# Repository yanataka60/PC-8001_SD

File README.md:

# PC-8001にSD-CARDからCMT形式ファイルのロード、セーブ機能

　PC-8001でSD-CARDからCMT形式ファイルのロード、セーブ機能を実現するものです。

　CMTからの読み込み実行に数分掛かっていたゲームも数十秒で実行できます。

　接続は、PC-8001本体後ろの拡張端子に接続しますが、50pフラットケーブルでの接続、50pカードエッジコネクタでの接続のどちらかを選択できます。

　なお、Arduino、ROMへ書き込むための機器が別途必要となります。

## 回路図
　KiCadフォルダ内のPC-8001_SD.pdfを参照してください。

　J5 2x25Pinコネクタを追加しています。

[回路図](https://github.com/yanataka60/PC-8001_SD/blob/main/Kicad/PC-8001_SD.pdf)

## 部品
|番号|品名|数量|備考|
| ------------ | ------------ | ------------ | ------------ |
||J1、J3のいずれか|||
|J1|2x25ボックスヘッダ|1|共立エレショップ JS-1200R-50など、秋月電子通商 PH-2x40RGなどのピンヘッダでも代用可(注1)(注5)|
|J3|50Pカードエッジコネクタ|1|せんごくネット通販 HRS CR22A-50D-2.54DSなど(注1)|
||J2、J4のいずれか|||
|J2|Micro_SD_Card_Kit|1|秋月電子通商 AE-microSD-LLCNV (注2) (注4)|
|J4|MicroSD Card Adapter|1|Arduino等に使われる5V電源に対応したもの (注4)|
|U1|74LS04|1||
|U2 U3|74LS30|2||
|U4|8255|1||
|U5|2764/28C64相当品|1||
|U6|Arduino_Pro_Mini_5V|1|Atmega328版を使用 168版は不可。(注3)|
|C1-C5|積層セラミックコンデンサ 0.1uF|5||
|C6|電解コンデンサ 16v100uF|1||
|S1|3Pスライドスイッチ|1|秋月電子通商 SS12D01G4など|
|S2|２回路２接点 スライドスイッチ|1|秋月電子通商 IS-2235-Gなど|
||ピンヘッダ|2Pin分|Arduino_Pro_MiniにはA4、A5用のピンヘッダが付いていないため別途調達が必要です 秋月電子通商 PH-1x40SGなど|
||ピンソケット(任意)|26Pin分|Arduino_Pro_Miniを取り外し可能としたい場合に調達します 秋月電子通商 FHU-1x42SGなど|
|J5|2x25Pinコネクタ|1|秋月電子通商 PH-2x40SGなど(注1)|

　　　注1)J1又はJ3のどちらかを選択して取り付けてください。

　　　注2)秋月電子通商　AE-microSD-LLCNVのJ1ジャンパはショートしてください。

　　　注3)Arduino Pro MiniはA4、A5ピンも使っています。

　　　注4)J2又はJ4のどちらかを選択して取り付けてください。

　　　注5)ピンヘッダで代用するときは、基板から若干浮かせてピンヘッダをハンダ付けするとフラットケーブをスムーズに抜き差しできます。

### MicroSD Card Adapterを使う
J4に取り付けます。

MicroSD Card Adapterについているピンヘッダを除去してハンダ付けするのが一番確実ですが、J4の穴にMicroSD Card Adapterをぴったりと押しつけ、裏から多めにハンダを流し込むことでハンダ付けをする方法もあります。なお、この方法の時にはしっかりハンダ付けが出来たかテスターで導通を確認しておいた方が安心です。

ハンダ付けに自信のない方はJ2の秋月電子通商　AE-microSD-LLCNVをお使いください。AE-microSD-LLCNVならパワーLED、アクセスLEDが付いています。

.JPG)

.JPG)

.JPG)

.JPG)

### その他必要なもの
　2x25Pinコネクタ(J1)を取り付けた場合には、本体との接続用ケーブルが必要となります。

　片側が2.54mmピッチ2x25Pinメスコネクタ、片側が2.54mmピッチ50pカードエッジコネクタのフラットケーブルを用意してください。

## ROMへの書込み
　Z80フォルダ内のEXT_ROM.binをROMライター(TL866II Plus等)を使って2764又は28C64に書き込みます。

## Arduinoプログラム
　Arduino IDEを使ってArduinoフォルダのPC-8001_SDフォルダ内PC-8001_SD.inoを書き込みます。

　SdFatライブラリを使用しているのでArduino IDEメニューのライブラリの管理からライブラリマネージャを立ち上げて「SdFat」をインストールしてください。

　「SdFat」で検索すれば見つかります。「SdFat」と「SdFat - Adafruit Fork」が見つかりますが「SdFat」のほうを使っています。

注)Arduinoを基板に直付けしている場合、Arduinoプログラムを書き込むときは、PC-8001本体とは接続を外し、74LS04を外したうえで書き込んでください。

## コネクタの取り付け
### 2x25Pinコネクタ(J1)を取り付ける場合
　取付穴は外側から１列目と２列目を使います。基板の表側に取り付けます。
.jpg)

### 50Pカードエッジコネクタ(J3)を取り付ける場合
　取付穴は外側から１列目と３列目を使います。基板の裏側に取り付けます。
.jpg)

## 接続
　PC-8001本体後ろの拡張端子に接続します。

#### 注)PC-8001本体後ろの拡張端子は経年劣化により接触不良となることが非常に多いです。動作不良の場合は一度、拡張端子を消しゴムで擦る、アルコールで拭く等掃除をしてみてください。

### フラットケーブルによる接続
.JPG)
.JPG)

### カードエッジコネクタによる接続
.JPG)
.JPG)

#### 私の入手したカードエッジコネクタでは基板と本体の間が充分に離れていますが、カードエッジコネクタによっては接触の危険があるかもしれません。気になる方はカプトンテープなどで裏面を保護してください。

## J5 2x25Pinコネクタを使ってRAMボード等接続する場合
　J5 2x25Pinコネクタは、拡張端子と同じ配列です。フラットケーブルを接続してRAMボード等を接続できますが、接続する向きを間違えないようにしてください。
.JPG)
.JPG)
.JPG)

## SD-CARD
　出来れば8GB以下のSDカードを用意してください。

　ArduinoのSdFatライブラリは、SD規格(最大2GB)、SDHC規格(2GB～32GB)に対応していますが、SDXC規格(32GB～2TB)には対応していません。

　また、SDHC規格のSDカードであっても32GB、16GBは相性により動作しないものがあるようです。

　FAT16又はFAT32が認識できます。NTFSは認識できません。

　ルートに置かれた拡張子が「.CMT」のCMT形式ファイルのみ認識できます。(CMT形式以外のファイル、フォルダも表示されますがLOAD実行の対象になりません)

　CMT形式であれば複数のCMTファイルを一つのファイルとしてまとめてあっても認識します。

　例)

　　BASIC+機械語　　　　　　　　　　　　　->　LOAD "DOSファイル名"[CR]、MON[CR]、L[CR]

　　機械語+機械語　　　　　　　　　　　　->　MON[CR]、 L DOSファイル名[CR]、L[CR]

　　オートラン機能ファイル+BASIC　　　　　->　MON[CR]、L DOSファイル名[CR]（以下オートラン）

　　オートラン機能ファイル+BASIC+機械語　->　MON[CR]、L DOSファイル名[CR]（以下オートラン）

　　オートラン機能ファイル+機械語+機械語　->　MON[CR]、L DOSファイル名[CR]（以下オートラン）

　　など

　ファイル名は「.CMT」を含めて31文字まで、ただし半角カタカナ、及び一部の記号はArduinoが認識しないので使えません。パソコンでファイル名を付けるときはアルファベット、数字および空白でファイル名をつけてください。

## 使い方

PC-8001_SDを使いたくない時には、PC-8001_SDを外してしまうのが簡単ですが、SHIFTキーを押してまま電源ON又はRESETすると拡張ROMは無効となります。

なお、N-BASIC Ver1.0で動作させるには起動直後に「DEF USR=&H6003:A=USR(0)」を実行してください。

### BASICコマンド
#### FILES[CR]又はFILES "文字列"[CR]
FILES[CR]とするとSD-CARDルートディレクトリにあるファイルの一覧を表示します。

FILES "文字列"[CR]とするとSD-CARDルートディレクトリにあるその文字列から始まるファイルの一覧を表示します。

20件表示したところで指示待ちになるので打ち切るならESC又は↑を入力すると打ち切られ、Bキーで前の16件に戻ります。それ以外のキーで次の16件を表示します。

　行頭に「LOAD "」を付加して表示してあるので実行したいファイルにカーソルキーを合わせて[CR]キーを押すだけでLOAD可能です。

　表示される順番は、登録順となりファイル名アルファベッド順などのソートした順で表示することはできません。

##### 参考
　FILES "文字列"[CR]とする場合、基本的にはダブルコーテーションが無くても機能しますが、数字で始まるファイル名の場合ダブルコーテーションが無いと検索できません。

　× FILES 3

　○ FILES "3"

#### LOAD "DOSファイル名"[CR]
指定したDOSフィル名のBASICプログラムをSD-CARDからLOADします。

ファイル名の前に"(ダブルコーテーション)は必須ですが、ファイル名の後ろに"(ダブルコーテーション)は有っても無くても構いません。

ファイル名の最後の「.CMT」も有っても無くても構いません。

　例)

　　LOAD "TEST" -> DOSファイル名「TEST.CMT」を読み込みます。

　　LOAD "TEST.BAS" -> DOSファイル名「TEST.BAS.CMT」を読み込みます。

　　LOAD "TEST.BAS.CMT" -> DOSファイル名「TEST.BAS.CMT」を読み込みます。

##### 参考
　基本的にはDOSファイル名をダブルコーテーションで括らなくても機能しますが、数字で始まるファイル名の場合ダブルコーテーションが無いとLOADできません。

　NOT FIND FILEと表示されます。

　× LOAD 3D MAZE

　○ LOAD "3D MAZE"

#### LOAD ""[CR]（※多段ロードファイルの２段目以降のみ有効）
直前に読み込まれたDOSファイルが多段ロード用に複数のCMTファイルが連結されており、２段目以降がBASICプログラムであった時のみ有効に動作し、BASICプログラムをSD-CARDからLOADします。

#### SAVE "DOSファイル名"[CR]
BASICプログラムを指定したDOSフィル名でSD-CARDに上書きSAVEします。

ファイル名の省略は出来ません。

ファイル名の前に"(ダブルコーテーション)は必須ですが、ファイル名の後ろに"(ダブルコーテーション)は有っても無くても構いません。

ファイル名の最後の「.CMT」も有っても無くても構いません。

指定したDOSファイル名の最初の６文字がCMT形式の中に保存されるファイル名として使われます。

BASICプログラムであることを識別するために「.BAS」を付けることを推奨します。

　例)

　　SAVE "TEST" -> 「TEST.CMT」で保存される。

　　SAVE "TEST.BAS" -> 「TEST.BAS.CMT」で保存される。

##### 参考
　基本的にはDOSファイル名をダブルコーテーションで括らなくても機能しますが、数字で始まるファイル名の場合ダブルコーテーションが無いとSAVEできません。

　SD-CARD INITIALIZE ERRORと表示されます。

#### KILL DOSファイル名[CR]
指定したDOSフィル名がSD-CARDに存在すればSD-CARDから削除します。

ファイル名の最後に「.CMT」も指定してもしなくても構いません。

##### 参考
　基本的にはDOSファイル名をダブルコーテーションで括らなくても機能しますが、数字で始まるファイル名の場合ダブルコーテーションが無いとKILLできません。

　NOT FIND FILEと表示されます。

　× KILL 3D MAZE

　○ KILL "3D MAZE"

### MONITORコマンド
#### F[CR]又はF 文字列[CR]
文字列を入力せずにF[CR]のみ入力するとSD-CARDルートディレクトリにあるファイルの一覧を表示します。

文字列を付けて入力すればSD-CARDルートディレクトリにあるその文字列から始まるファイルの一覧を表示します。

20件表示したところで指示待ちになるので打ち切るならESC又は↑を入力すると打ち切られ、Bキーで前の16件に戻ります。それ以外のキーで次の16件を表示します。

　行頭に「*L 」を付加して表示してあるので実行したいファイルにカーソルキーを合わせて[CR]キーを押すだけでLOAD可能です。

　表示される順番は、登録順となりファイル名アルファベッド順などのソートした順で表示することはできません。

##### 例)
　　F[CR]

　　F S[CR]

　　F SP[CR]

#### L DOSファイル名[CR]
指定したDOSフィル名の機械語プログラムをSD-CARDからLOADします。

ファイル名の最後の「.CMT」は有っても無くても構いません。

　例)

　　L TEST -> DOSファイル名「TEST.CMT」を読み込みます。

　　L TEST.BIN -> DOSファイル名「TEST.BIN.CMT」を読み込みます。

　　L TEST.BIN.CMT -> DOSファイル名「TEST.BIN.CMT」を読み込みます。

#### L[CR]（※多段ロードファイルの２段目以降のみ有効）
直前に読み込まれたDOSファイルが多段ロード用に複数のCMTファイルが連結されており、２段目以降が機械語プログラムであった時のみ有効に動作し、機械語プログラムをSD-CARDからLOADします。

#### W 16進数4桁 16進数4桁 DOSファイル名[CR]
1番目の16進数4桁が表すアドレスから2番目の16進数4桁が表すアドレスまでを指定したDOSファイル名でSD-CARDに機械語として上書き保存します。

ファイル名の最後に「.CMT」を指定してもしなくても構いません。

またWの後ろや各パラメータ間に空白が有っても無くても構いません。

機械語プログラムであることを識別するために「.BIN」等を付けることを推奨します。

　例)

　　W 0000 001F TEST -> 　　0000番地から001F番地までをDOSファイル名「TEST.CMT」で保存する。

　　W 0000 001F TEST.BIN -> 0000番地から001F番地までをDOSファイル名「TEST.BIN.CMT」で保存する。

#### G 16進数4桁[CR]
16進数4桁が表すアドレスにジャンプします。

Gの後ろに空白があっても無くても構いません。

#### B[CR]
BASICに復帰します。MONITORでのコマンド入力をスクリーンエディタにしたため、CTRL+Bが機能しないので代替コマンドです。

CTRL+Cと動作は同じです。

#### CTRL+C
BASICに復帰します。MONITORでのコマンド入力をスクリーンエディタにしたため、CTRL+Bが機能しないので代替コマンドです。

B[CR]と動作は同じです。

#### S 16進数4桁 {16進数2桁}の繰り返し[CR]
PC-8001のメモリに16進数4桁が表すアドレスから16進数2桁が表すデータを書き込みます。

[CR]で改行すると有効な16進数2桁データを書き込んだ後、次に書き込みとなるアドレスを表示しますので続きの16進数2桁のデータを入力して[CR]で改行します。

アドレス表示の次に16進数2桁のデータを入力せずに[CR]を押すと終了します。

Sの後ろ、アドレス、データの区切りに空白が有っても無くても構いません。

例)

以下の例はすべて同じ結果となります。

　SA0001122334455

　SA000 11 22 33 44 55

　S A000 1122334455

　S A0001122334455

　S A000 1122 3344 55

#### D 16進数4桁[CR]
16進数4桁が表すアドレスからPC-8001のメモリの内容を128Byteを一画面として表示します。

一画面表示したところで「NEXT:ANY BACK:B BREAK:ESC」と表示して指示待ちとなるのでBで前の128Byteを表示、ESCで中止、それ以外のキーで次の128Byteの表示となります。

一画面表示している途中でもESCでいつでも中止できます。

### ファンクションキーを利用したオートラン機能
ファンクションキーを利用したオートラン機能に対応していますが、一部オリジナルと異なる点があります。

そこでオートラン機能ファイルをロードする時にPC-8001_SDの仕様に自動変換する機能を付けました。(2022.8.21実装)

以下の修正点についてオートラン機能ファイルをロードする時に自動的に修正ロードされますのでオートラン機能ファイルを修正する必要はありません。当然、修正してあっても機能します。

自動で修正される点

　1　CTRL+BではMONITORからBASICへ復帰できません。CTRL+Cに修正されます。

　2　SD-CARDからのBASICプログラムをLOADするコマンドは「LOAD」で、1本のCMTファイルとなっていればファイル名を指定する必要もありませんので「CLOAD"ファイル名"」は「LOAD""」に修正されます。

## 操作上の注意
　~~「SD-CARD INITIALIZE ERROR」と表示されたときは、SD-CARDをいったん抜き再挿入したうえでArduinoをリセットしてください。~~

　~~SD-CARDにアクセスしていない時に電源が入ったままで SD-CARDを抜いた後、再挿入しSD-CARDにアクセスすると「SD-CARD INITIALIZE ERROR」となる場合があります。再挿入した場合にはSD-CARDにアクセスする前にArduinoを必ずリセットしてください。~~

　~~SD-CARDの抜き差しは電源を切った状態で行うほうがより確実です。~~

　(2024.3.12) SD-CARDにアクセスしていない時に電源が入ったままでSD-CARDを抜くと再度SD-CARDを挿入してもSD-CARDにアクセスできない問題を解消しました。(Arduinoを最新版に書き換えてください)

　再度SD-CARDを挿入した後、FILES、LOAD、SAVE等でSD-CARDに3回ほどアクセスすれば復旧します。

## New City HeroをSDから読み込み実行するための修正
　PC-8001_SDは内藤 時浩さんが頒布されているNew City HeroをPC-8001実機で手軽に遊びたいが為に作ったといっても過言ではありません。

　New City Heroは機械語の多段ロード方式で２段目のプログラム内にCMTからの読み込みルーチンをコールしている箇所がありますので、そこをSDから読み込むためのコール先に修正する必要があります。

　New City HeroのCMT形式ファイルに次の手順で修正を行いPC-8001_SD用のCMT形式ファイルを作り、SD-CARDに保存してください。

　1　頒布していただいたNew City HeroのCMTファイルをbugfire2009さんの「DumpListEditor」にDrag&Dropする

　2　「BASIC入力」タブをクリックして言語「Patch File」を選択する。

　3　表示されているPathc File Sampleをすべて削除し、次の15行に入れ替える。

/CD,F3,0B/=00,00,00

/CD,9E,5F/=CD,06,60

/CD,9E,5F/=CD,06,60

/CD,9E,5F/=CD,06,60

/CD,9E,5F/=CD,06,60

/CD,9E,5F/=CD,06,60

/CD,9E,5F/=CD,06,60

/CD,9E,5F/=CD,06,60

/CD,9E,5F/=CD,06,60

/CD,9E,5F/=CD,06,60

/CD,9E,5F/=CD,06,60

/CD,9E,5F/=CD,06,60

/CD,9E,5F/=CD,06,60

/CD,9E,5F/=CD,06,60

/CD,9E,5F/=CD,06,60

　4　「ファイル整理画面にPaste」を押す。

　5　ファイル整理画面に「PATCH.patch」というファイルが追加される。ファイルの位置はどこにあっても可。

　6　「cmt書出し」を押してPC-8001_SD対応済cmtファイルとして保存する。

## DumpListEditor動画作成機で作られたCMTファイルへの対応

　DumpListEditor動画作成機で作られたCMTファイルのうち、「Chain(cmt出力時のみ)」をチェックして作られたプログラムはCMTルーチンをコールしますので修正が必要となります。

セミグラ作成機＆動画作成機

https://bugfire2009.ojaru.jp/semigra/

で紹介されているきらびぃさん作成の

「メガCD版シルフィードのデモをPC8001で再生してみたフル版(修正版)」

「PC8001でBad Apple全編をcmt化」

の二つがこの機能を使っていますのでPC-8001_SDで再生するにはパッチ当てが必要になります。

　なお、以下の方法でPATCHを当てると最後のシーンが無限ループします。最後のファイルにはPATCHを当てないでおけば止まるのですが、手軽にPATCHを当てられますのでご容赦ください。

### 「メガCD版シルフィードのデモをPC8001で再生してみたフル版(修正版)」修正手順
　1　CMTファイルを「DumpListEditor」にDrag&Dropする。

　2　「BASIC入力」タブをクリックして言語「Patch File」を選択する。

　3　表示されているPathc File Sampleをすべて削除し、次の2行に入れ替える。

/CD,3A,5F,30/=CD,09,60,18

/E6,04,20,09/=E6,04,18,09

　4　「ファイル整理画面にPaste」を押す。

　5　ファイル整理画面に「PATCH.patch」というファイルが追加される。ファイルの位置はどこにあっても可。

　6　「cmt書出し」を押してPC-8001_SD対応済cmtファイルとして保存する。

### 「PC8001でBad Apple全編をcmt化」修正手順

　基本的に「メガCD版シルフィードのデモをPC8001で再生してみたフル版(修正版)」の修正手順と同じです。

## RAMボートとの共存について
　バンク切替をサポートした以下のRAMボートとの共存、動作確認済みです。

　　ちくらっぺさん設計の「32kB拡張RAM基板」

　　KUNI-NET元シソペさん設計の「PC-8001用 128kバイトメモリーボード」

#### PSA基板に増設する拡張メモリー基板で動作しないとの報告を頂きました。
#### PSA基板に増設する拡張メモリー基板の仕様を確認したところ、拡張ROM領域を単純にRAMに置き換えることを目的として設計されており、バンク切替動作をサポートしていないため共存できません。

　S2のROMDS3を「EXT」にすることでポートE2hを制御して$0000～$7FFFの空間をROM→RAM切替するボードと共存できます。

　S1のSD→CMT切替は機能しなくなりますが、どちらかにしておいてください。

　PC-8001_SDを繋いだままPC-8001_SDのROMを無効にしたい場合はS2のROMDS3を「FIX」、S1のSD→CMT切替を「CMT」にしてください。

## SDアクセスサービスルーチン
　「プログラム側からファイル名を指定してSDから読み込む」機能と「プログラム側からファイル名を指定してSDへ書き込む」機能を追加しました。

#### 　この機能を活用するには、この機能に対応したアプリケーションプログラムが必要となります。

　以下にサービスルーチンの仕様とエントリポイントを公開します。

|エントリポイント|名前|用途|
| -------------- | -- | -- |
|600F|ROPEN|READ FILE OPEN|

　HL <- DOS_FILENAME先頭アドレス

　HLレジスタが示すDOS_FILENAMEで読み込み用ファイルをオープン

　DOS_FILENAMEは31文字まで、最後に00Hをつけること。

　フラグレジスタ以外のレジスタは変化しない。

　正常終了 CF=0、異常終了 CF=1

|エントリポイント|名前|用途|
| -------------- | -- | -- |
|6006|D_5F9E|5F9EH代替|

　読み出されたデータ -> A

　読み込み用としてOPENしているファイルから1BYTE読み出し

|エントリポイント|名前|用途|
| -------------- | -- | -- |
|6009|H_5F3A|5F3AH代替|

　読み出しオープンされているファイルから機械語フォーマットで保存されている機械語を読み出す。

　WORK AREA:FF3D～FF3E メモリ書き込み開始アドレス

　正常終了 CF=0、異常終了 CF=1

|エントリポイント|名前|用途|
| -------------- | -- | -- |
|600C|MONHOT|5C66H代替|

　Gコマンドで実行する機械語プログラムからモニタに戻るときには、ここへのジャンプを指定。

　オートラン機能が実行中であれば継続して実行される。

|エントリポイント|名前|用途|
| -------------- | -- | -- |
|6012|WAOPEN|WRITE FILE APPEND OPEN|

　HL <- DOS_FILENAME先頭アドレス

　HLレジスタが示すDOS_FILENAMEで追加書き込み用としてファイルをオープン

　DOS_FILENAMEは31文字まで、最後に00Hをつけること。

　フラグレジスタ以外のレジスタは変化しない。

　正常終了 CF=0、異常終了 CF=1

|エントリポイント|名前|用途|
| -------------- | -- | -- |
|601B|WNOPEN|WRITE FILE NEW OPEN|

　HL <- DOS_FILENAME先頭アドレス

　HLレジスタが示すDOS_FILENAMEで書き込み用として新たにファイルをオープン。同名のDOS_FILENAMEのファイルがある場合は削除したのちにオープンする。

　DOS_FILENAMEは31文字まで、最後に00Hをつけること。

　フラグレジスタ以外のレジスタは変化しない。

　正常終了 CF=0、異常終了 CF=1

|エントリポイント|名前|用途|
| -------------- | -- | -- |
|6018|D_5F2F|5F2FH代替|

　A <- 書き込みデータ

　書込み用でオープンされているファイルにAレジスタのデータを追加書込みする。

　フラグレジスタ以外のレジスタは変化しない。

　正常終了 CF=0、異常終了 CF=1

|エントリポイント|名前|用途|
| -------------- | -- | -- |
|6015|D_5ED9|5ED9H代替|

　HL <- 書き込み開始アドレス

　DE <- 書き込み終了アドレス

　書込み用でオープンされているファイルに書き込み開始アドレスから書き込み終了アドレスまでのメモリ内容を機械語フォーマットで書出し、クローズする。

　WORK AREA:FF3D～FF3E 書き込み開始アドレス

　　　　　　　FF3F～FF40 書き込み終了アドレス

　正常終了 CF=0、異常終了 CF=1

|エントリポイント|名前|用途|
| -------------- | -- | -- |
|601E|WCLOSE|WRITE FILE CLOSE|

　書込み用ファイルをクローズする。

　フラグレジスタ以外のレジスタは変化しない。

　正常終了 CF=0、異常終了 CF=1

### SDアクセスサービスルーチンのテスト用プログラム
　SDアクセスサービスルーチンのテストと使い方のサンプルとしてZ80フォルダ内SD Access service routine Testフォルダにテストプログラムを置きました。

　「sd_test.BIN.CMT」と「SD_TEST2.BIN.CMT」の二つをSDカードにコピーしてモニタ Lコマンドで「sd_test.BIN.CMT」を読み込み実行してください。

　画面に01からFFまで表示した後、「SD TEST OK」と表示して終了します。

　SDカードには「SD_WRITE_READ_TEST.DAT」と「SD_WRT_DIRECT_TEST.BIN.CMT」の二つのファイルが出来上がっているはずです。

　「SD_WRITE_READ_TEST.DAT」は510Byteのファイルサイズで01からFF、FFから01までのデータが格納されているはずです。

　「SD_WRT_DIRECT_TEST.BIN.CMT」は161ByteのファイルサイズでA000h～A096hまでのメモリ内容を機械語フォーマットのcmtとして保存した内容となっているはずです。

## 謝辞
　基板の作成に当たり以下のデータを使わせていただきました。ありがとうございました。

　Arduino Pro Mini

　　https://github.com/g200kg/kicad-lib-arduino

　AE-microSD-LLCNV

　　https://github.com/kuninet/PC-8001-SD-8kRAM

　New City Heroの修正点を公開することを快く承諾してくださった内藤 時浩様、ありがとうございました。

　NBASICのコマンド追加に当たっては、ちくらっぺ様のSD-DOSがとても参考になりました。ありがとうございました。

　　https://github.com/chiqlappe/SD-DOS

　DumpListEditorの動画作成機で作成されたcmtファイルへの修正方法を公開することを快く承諾してくださったbugfire2009様、ありがとうございました。

　スタック領域を破壊し正常にロードが出来ない機械語プログラムの事例について情報を提供してくださった久保ちゃん様、ありがとうございました。

## 追記
2022.7.23

　BASICから機械語ファイルをLOADしようとしたときのエラーメッセージを修正しました。

2022.7.24

　FILES 文字列[CR]としたときにSYNTAX ERRORとなる事象を修正しました。これにより「FILSE SEARCH:」と聞いてくる仕様は廃止。

2022.7.25

　FILESを↑キーで打ち切ったとき、時々Syntax Errorが発生するため2行戻す動きを廃止

　FILES及びFコマンドの説明中誤りがあったので修正

　　一回で表示される行数　誤)20行　正)16行

　　打ち切るキー　誤)SHIFT+BREAK　正)ESC

2022.7.27

　DOSファイル名での拡張子について曖昧な記述があったので修正しました。

2022.8.4

　Arduinoを基板に直付けしている場合、Arduinoプログラムを書き込むときの注意点を書き加えました。

　Kicadライブラリ設定を修正しました。

　BASICでSyntax Errorが表示される事象に対応するためEXT_ROMプログラムに修正を加えました。

2022.8.14

　EXTROM.BINを修正

　　MONITOR Gコマンドの処理でPOP BCが抜けていたので追加。

　　mk2用と統合

　　　拡張ROM認識コードを041H,042H,00Hとした。

　　　SHIFTキーを押しながら起動することで拡張ROMを有効にするか選択できるようにした。(mk2用)

　　　mk2においてもfiles、save、killコマンドでSyntaxErrorが出ないように修正

2022.8.18

　DumpListEditorの動画作成機機能で作成されたきらびぃさん作成の「メガCD版シルフィードのデモをPC8001で再生してみたフル版(修正版)」、「PC8001でBad Apple全編をcmt化」の修正方法を追加しました。

2022.8.21

　MONITOR Lコマンドで読み込み時にオートラン機能ファイルであればCTRL+B、CLOADをSD用に書き換えるようにした。

2022.8.22

　N-BASIC Ver1.0では動作しない旨を追記、カードエッジコネクタでの接続時に裏面の保護について追記。

　N-BASIC Ver1.0で動作させる方法を追記。

2022.8.31

　RAMボードと共存するための改造方法を追記。

2022.9.18

　PSA基板に増設する拡張メモリー基板とは共存できないことを追記

2022.9.25

　MicroSD Card Adapter用の端子、ROMDS3制御切り替えスイッチを付加し、基板をRev1.2に更新。

2023.5.30

　E800h以降までロードする機械語プログラムをロードするとスタック領域を破壊してしまうことに対処。

2023.6.3

　mk2用ソースの修正のためEXT_ROM.sを修正。

2023.6.10

　SDアクセスサービスルーチンを追加、エントリポイントを公開。5F3AH代替ルーチンを見直し。

2023.8.11

　Rev1.4基板を追加しました。

2023.9.11

　N-BASIC V1.0の場合、MONITORに入ることでPC-8001_SDの初期化が行われるように修正。

2023.10.5

　ファイル名長さの仕様を訂正

　　誤)「.CMT」を除いて32文字      正)「.CMT」を含めて31文字

2024.1.15

　SDカードは8GB以下が望ましいことを追記。

2024.3.12

　電源が入ったままでSD-CARDを抜くと再度SD-CARDを挿入してもSD-CARDにアクセスできない問題を解消した。

2024.9.11

　サービスルーチンでの使用ワークエリアを追記

2025.1.29

　コネクタの記述を修正しました。

2025.8.15

　PC-8001本体後部拡張端子の接触不良について追記。PC-8001mk2_SDとのソースコード互換性確保のためN-BASICV1.0判別ルーチンを後ろに移動。

2025.8.30

　サービスルーチンで解説していなかった600Ch(MONHOT)の解説を追加。

2026.8.16

　旧基板用の記述を整理しました。

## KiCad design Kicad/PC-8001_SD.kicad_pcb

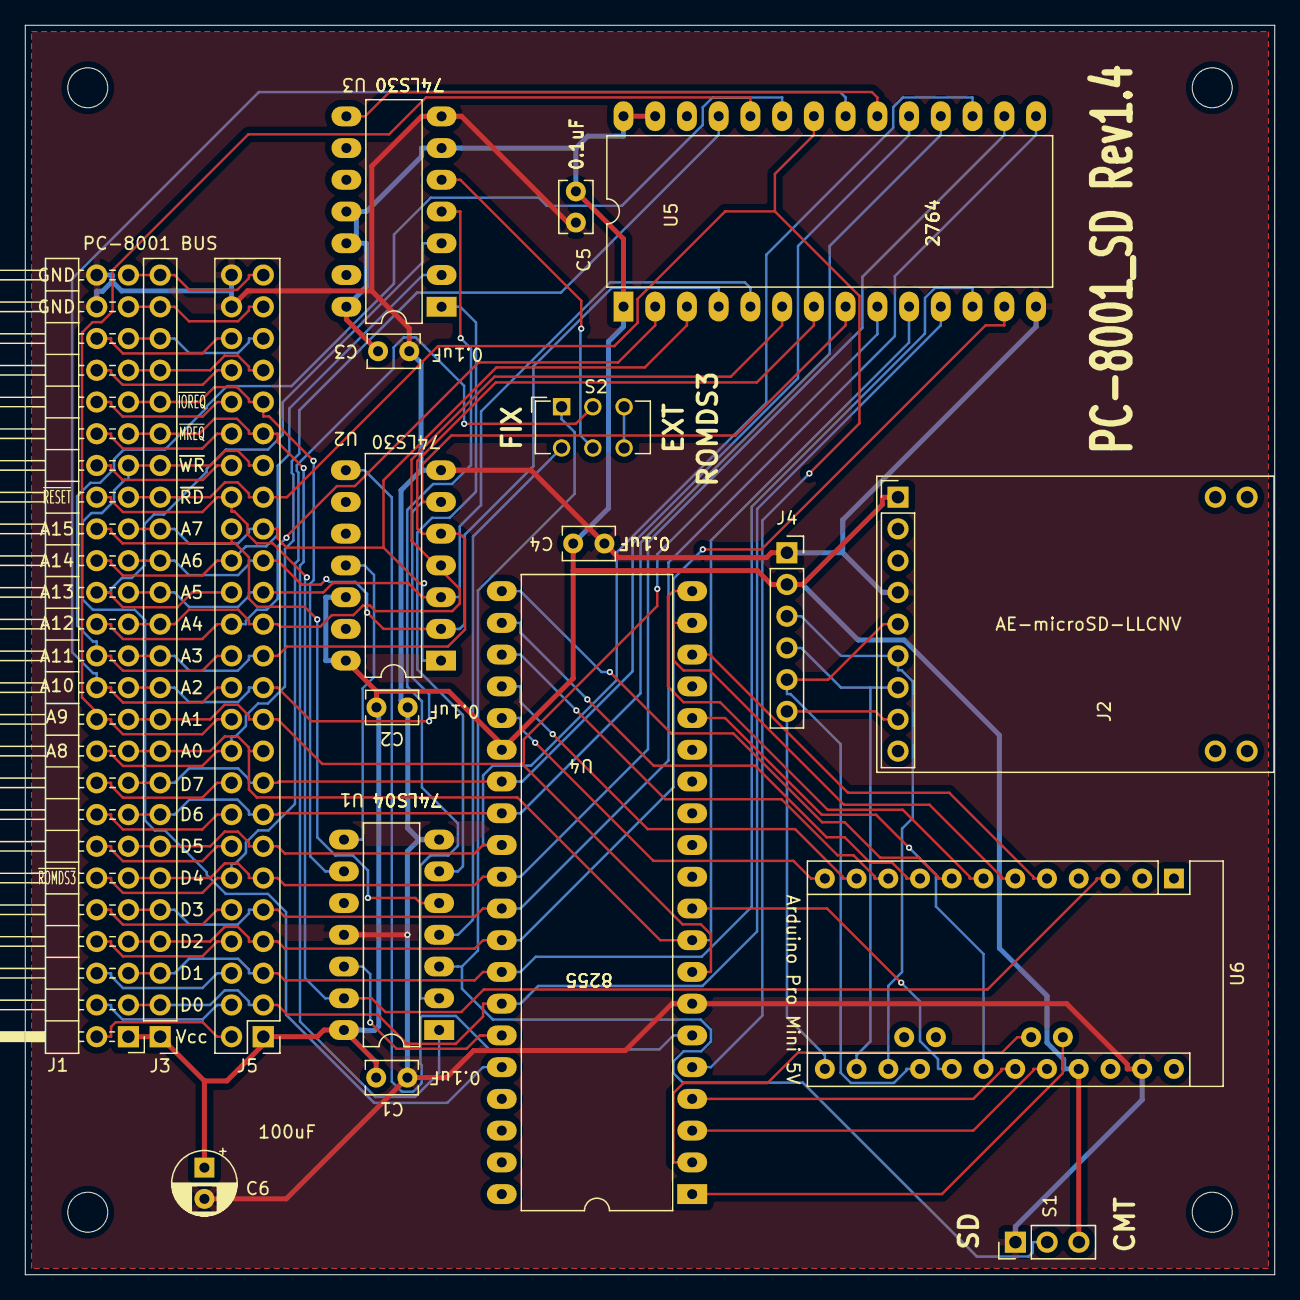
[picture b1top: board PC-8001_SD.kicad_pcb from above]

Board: 2 copper layers, 100.0 x 100.0 mm, 23 parts (0 on the bottom side), 77 nets.

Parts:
C1, C2, C3, C4, C5: 0.1uF; C_Rect_L4.0mm_W2.5mm_P2.50mm
C6: 100uF; CP_Radial_D5.0mm_P2.50mm
J1: PC-8001 BUS; PinHeader_2x25_P2.54mm_Horizontal
J2: Micro_SD_Card_Kit; AE-microSD-LLCNV
J3: Conn_01x25; PinHeader_1x25_P2.54mm_Vertical
J4: MicroSD Card Adapter; PinSocket_1x06_P2.54mm_Vertical
J5: PC-8001 BUS; PinHeader_2x25_P2.54mm_Vertical
MH1, MH2, MH3, MH4: MountingHole_3.2mm_M3
S1: SLIDE_SWITCH_3P; PinHeader_1x03_P2.54mm_Vertical
S2: SLIDE SWITCH; SW_CuK_JS202011CQN_DPDT_Straight
U1: 74LS04; DIP-14_W7.62mm_LongPads
U2, U3: 74LS30; DIP-14_W7.62mm_LongPads
U4: 8255; DIP-40_W15.24mm_LongPads
U5: 2764; DIP-28_W15.24mm_LongPads
U6: Arduino_Pro_Mini_5V; Arduino_Pro_Mini

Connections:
+5V: C1.2, C2.2, C3.2, C4.1, C5.1, C6.1, J1.1, J2.1, J3.1, J4.2, J5.1, S1.3, U1.14, U2.12, U2.14, U3.6, U3.11, U3.12, U3.14, U4.26, U5.1, U5.27, U5.28, U6.21
/+12V: J1.2, J5.2
/-12V: J1.4, J5.4
/A0: J1.19, J3.10, J5.19, U4.9, U5.10
/A1: J1.21, J3.11, J5.21, U4.8, U5.9
/A2: J1.23, J3.12, J5.23, U2.6, U5.8
/A3: J1.25, J3.13, J5.25, U2.5, U5.7
/A4: J1.27, J3.14, J5.27, U2.4, U5.6
/A5: J1.29, J3.15, J5.29, U2.3, U5.5
/A6: J1.31, J3.16, J5.31, U2.2, U5.4
/A7: J1.33, J3.17, J5.33, U2.1, U5.3
/A8: J1.20, J5.20, U5.25
/A9: J1.22, J5.22, U5.24
/A10: J1.24, J5.24, U5.21
/A11: J1.26, J5.26, U5.23
/A12: J1.28, J5.28, U5.2
/A13: J1.30, J5.30, U3.3
/A14: J1.32, J5.32, U3.2
/A15: J1.34, J5.34, U1.5
/CS: J2.8, J4.6, U6.13
/D0: J1.3, J3.2, J5.3, U4.34, U5.11
/D1: J1.5, J3.3, J5.5, U4.33, U5.12
/D2: J1.7, J3.4, J5.7, U4.32, U5.13
/D3: J1.9, J3.5, J5.9, U4.31, U5.15
/D4: J1.11, J3.6, J5.11, U4.30, U5.16
/D5: J1.13, J3.7, J5.13, U4.29, U5.17
/D6: J1.15, J3.8, J5.15, U4.28, U5.18
/D7: J1.17, J3.9, J5.17, U4.27, U5.19
/MISO: J2.6, J4.3, U6.15
/MOSI: J2.7, J4.4, U6.14
/PHAI: J1.49, J3.25, J5.49
/SCK: J2.5, J4.5, U6.16
/SCLOCK: J1.47, J3.24, J5.47
/~EXTON: J1.18, J5.18
/~INT: J1.14, J5.14
/~IOREQ: J1.41, J3.21, J5.41, U1.9
/~M1: J1.45, J3.23, J5.45
/~MREQ: J1.39, J3.20, J5.39, U1.1
/~MUX: J1.42, J5.42
/~NMI: J1.16, J5.16
/~RAS0: J1.44, J5.44
/~RAS1: J1.46, J5.46
/~RD: J1.35, J3.18, J5.35, U4.5, U5.22
/~RESET: J1.36, J5.36, U1.13, U6.3
/~RFSH: J1.43, J3.22, J5.43
/~ROMDS0: J1.6, J5.6
/~ROMDS1: J1.8, J5.8
/~ROMDS2: J1.10, J5.10
/~ROMDS3: J1.12, J5.12, S2.2
/~WAIT: J1.38, J5.38
/~WE: J1.40, J5.40
/~WR: J1.37, J3.19, J5.37, U4.36
GND: C1.1, C2.1, C3.1, C4.2, C5.2, C6.2, J1.48, J1.50, J2.4, J4.1, J5.48, J5.50, S1.1, U1.7, U1.11, U2.7, U3.7, U4.7, U5.14, U6.23
unnamed: S1.2, S2.1, U1.3
unnamed: S2.3, S2.6
unnamed: S2.4, U1.4
unnamed: S2.5, U3.5
unnamed: U1.2, U3.4
unnamed: U1.6, U3.1
unnamed: U1.8, U2.11
unnamed: U1.12, U4.35
unnamed: U2.8, U4.6
unnamed: U3.8, U5.20
unnamed: U4.1, U6.A5
unnamed: U4.2, U6.A4
unnamed: U4.3, U6.20
unnamed: U4.4, U6.19
unnamed: U4.10, U6.17
unnamed: U4.16, U6.18
unnamed: U4.18, U6.5
unnamed: U4.19, U6.6
unnamed: U4.20, U6.7
unnamed: U4.21, U6.8
unnamed: U4.22, U6.9
unnamed: U4.23, U6.10
unnamed: U4.24, U6.11
unnamed: U4.25, U6.12
